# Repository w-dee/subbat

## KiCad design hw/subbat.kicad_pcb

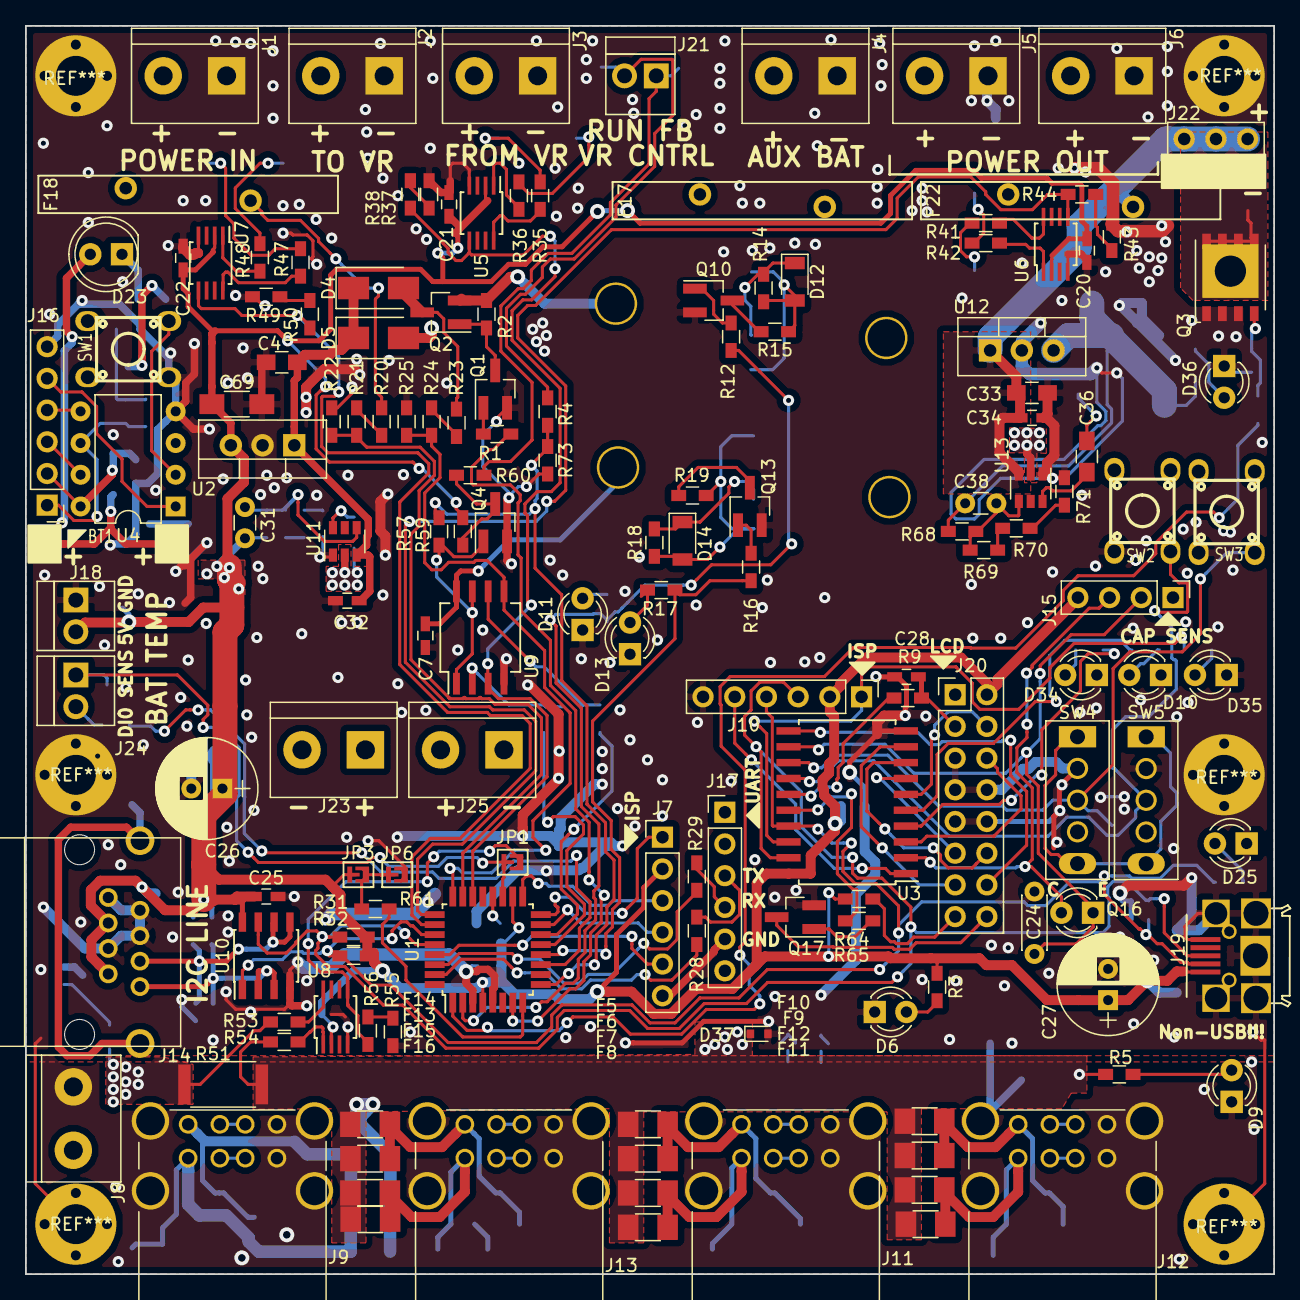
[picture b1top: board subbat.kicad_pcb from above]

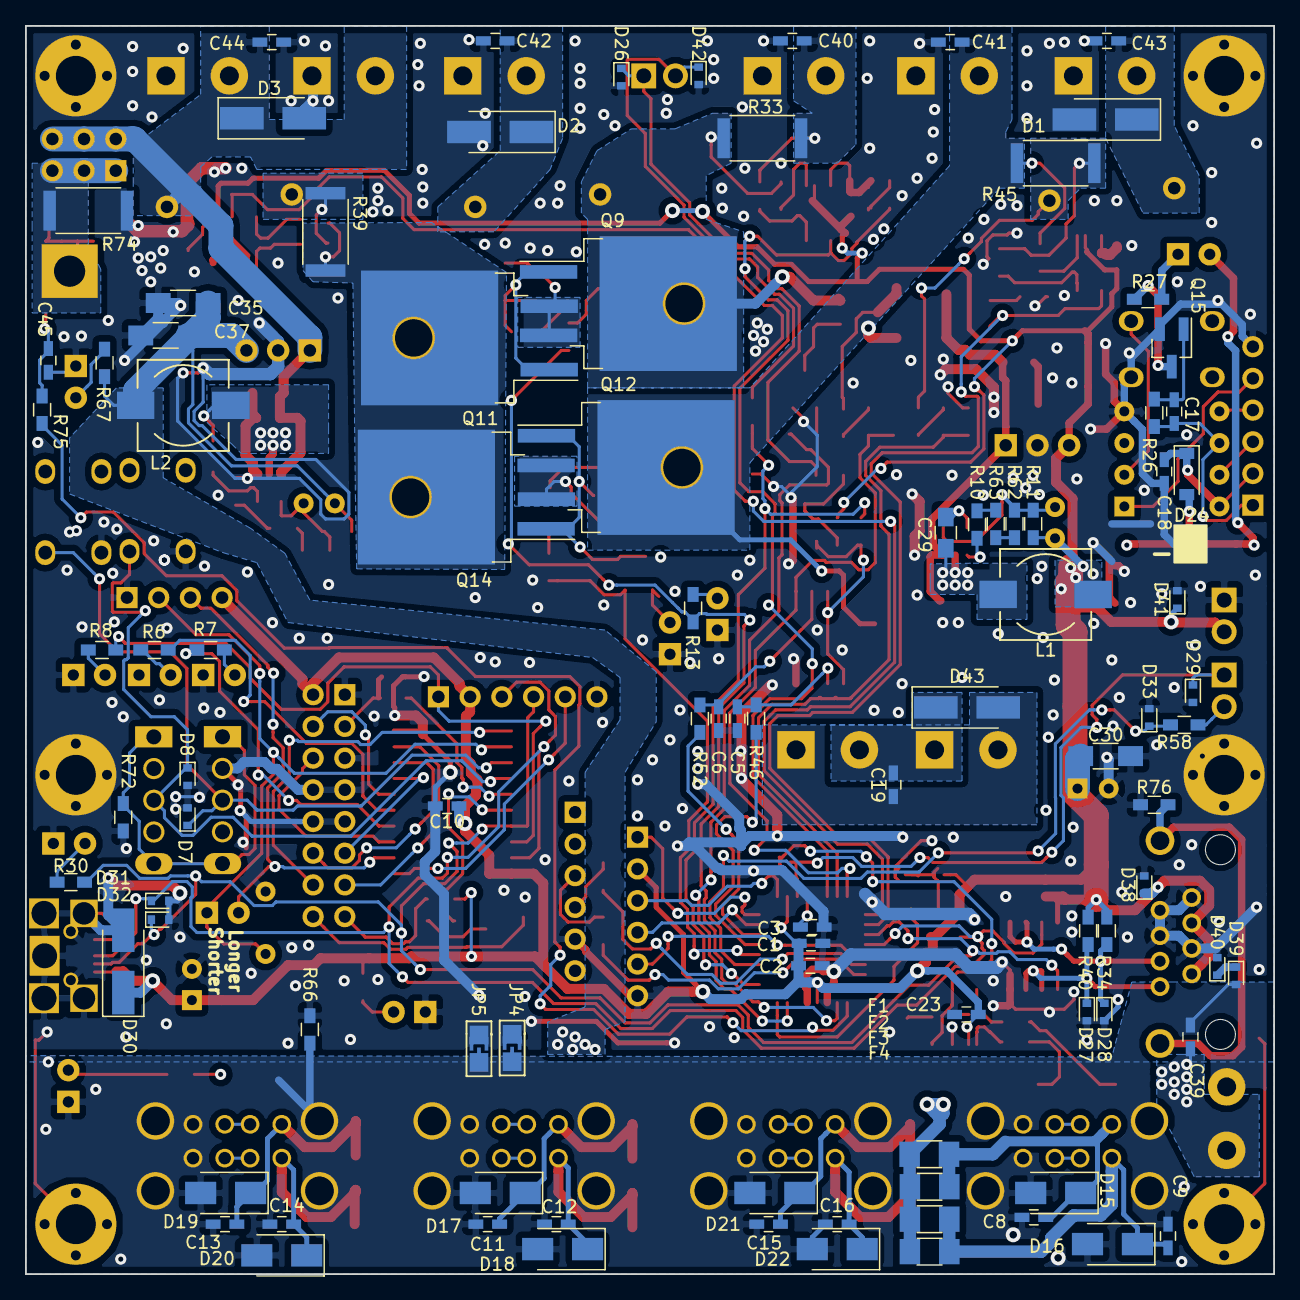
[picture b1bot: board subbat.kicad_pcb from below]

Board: 2 copper layers, 100.0 x 100.0 mm, 248 parts (95 on the bottom side), 149 nets.

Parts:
BT1: Battery_Cell; CR2032HOLDER_SIDE_SHORT
C1, C2, C3, C5, C6, C7, C8, C9, C10, C11, C12, C13, C14, C15, C16, C18, C19, C20, C21, C22, C23, C25, C28, C32, C34, C39, C40, C41, C42, C43, C44: 1u; C_0603_HandSoldering
C4, C33: 4.7u 50V; C_0805_HandSoldering
C17: 220p; C_0603_HandSoldering
C24: 0.1u; C_Disc_D4.3mm_W1.9mm_P5.00mm
C26: 100u; CP_Radial_D8.0mm_P2.50mm
C27: CP1_Small; CP_Radial_D8.0mm_P2.50mm
C29, C36: 0.1u 50V; C_0805_HandSoldering
C30, C35, C37, C69: 10u; C_1206_HandSoldering
C31, C38: 75p; C_Disc_D3.0mm_W1.6mm_P2.50mm
C45: 1u DNI; C_0603_HandSoldering
D1, D2, D3, D43: 30V; D_SMA_Handsoldering
D4, D5: D_Schottky; D_SMA
D6, D9, D10, D11, D13, D25, D34, D35, D36: LED; LED_D3.0mm
D7, D8, D26, D27, D28, D29, D31, D32, D33, D37, D38, D39, D40, D41, D42: ESD5Z5.0T1G; D_SOD-523
D12, D14: 12V; D_1206
D15, D16, D17, D18, D19, D20, D21, D22: 6V; D_SMA
D23: IR LED; LED_D5.0mm
D24: D_Schottky; D_SOD-123
D30: 6V; D_SMA_Handsoldering
F1, F2, F3, F4, F5, F6, F7, F8, F9, F10, F11, F12, F13, F14, F15, F16: 2A; Fuse_SMD1206_Wave
F17, F18, F22: 9A hold, 18A trip; POLYSWITCH_W24_P10
J1, J2, J3, J4, J5, J6, J8, J23, J25: Conn_01x02; TerminalBlock_bornier-2_P5.08mm
J7, J10, J16, J17: Conn_01x06_Male; Pin_Header_Straight_1x06_Pitch2.54mm
J9, J11, J12, J13: USB_Ax2
J14: RJ45; RJ45_8_Neltron-7810
J15: Conn_01x04_Male; Pin_Header_Straight_1x04_Pitch2.54mm
J18, J21, J24: Conn_01x02; TerminalBlock_2_P_2.54mm_without_hole
J19: USB_B_Micro; USB-MICRO-B-RECEPT-UNIVERSAL
J20: Conn_02x08_Odd_Even; Pin_Header_Straight_2x08_Pitch2.54mm
J22: Conn_02x03_Odd_Even; Pin_Header_Straight_2x03_Pitch2.54mm
JP1, JP3: Jumper_NO_Small; SolderJumper
JP4, JP5: Jumper_NO_Small; SolderJumper_L
JP6: Jumper_NC_Small; SolderJumper
L1, L2: 22u; Choke_SMD_7.3x7.3_H3.5_handsoldering
Q1, Q4, Q10, Q13, Q15, Q17: Q_NPN_BEC; SOT-23_Handsoldering
Q2: Q_PMOS_GSD; SOT-23_Handsoldering
Q3: TPH11006NL; TDSON-8-1_HandSoldering_mod
Q9, Q11, Q12, Q14: AOD403; TO-263-2-with-holes
Q16: Q_Photo_NPN_EC; LED_D3.0mm
R1, R12, R15, R16, R19, R21, R24, R26, R57, R59, R62, R65, R69, R73: 10k; R_0603_HandSoldering
R2, R14, R18, R66: 470k; R_0603_HandSoldering
R3, R4, R5, R6, R7, R8, R13, R17, R30, R60, R63, R67, R70: 2.2k; R_0603_HandSoldering
R9, R11, R46, R52, R68: 100k; R_0603_HandSoldering
R10, R22, R25, R34, R37, R40, R43, R49, R55, R71: 1k; R_0603_HandSoldering
R20, R23, R61: 22k; R_0603_HandSoldering
R27, R75: 10R; R_0603_HandSoldering
R28, R29, R35, R36, R38, R41, R42, R44, R47, R48, R50, R53, R54, R56, R58: 120R; R_0603_HandSoldering
R31, R32: 4.7k; R_0603_HandSoldering
R33, R39, R45, R51: 0.01R; R_2512
R64: 680; R_0603_HandSoldering
R72, R76: 1M; R_0603_HandSoldering
R74: 10R 2W@long, 20W@1 sec; R_2512
SW1, SW2, SW3: SW_Push; TACT-SW-4P
SW4, SW5: SW_SPDT_WITH_SHIELD; SW_SPDT_WITH_SHILD
U1: ATMEGA328P-AU; TQFP-32_7x7mm_Pitch0.8mm
U2, U12: L7803; TO-220-3_Vertical
U3: ATTINY2313-20SU; SOIC-20W_7.5x12.8mm_Pitch1.27mm
U4: ATTINY13A-SSU; DIP-8_W7.62mm
U5, U6, U7, U8: LT6105; MSOP-8_3x3mm_Pitch0.65mm-thin
U9: LM393; SO-8_5.3x6.2mm_Pitch1.27mm
U10: P82B96; SOIC-8_3.9x4.9mm_Pitch1.27mm
U11, U13: TPS54202; SOT-23-6

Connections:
+5V: C1.1, C2.1, C10.1, C20.1, C21.1, C22.1, C23.1, C25.1, C26.1, C27.1, C30.1, C31.1, C69.1, D30.1, D38.1, D41.1, J7.2, J10.2, J14.2, J14.6, J15.4, J18.2, J19.1, J20.2, JP3.2, L1.1, R3.1, R11.1, R31.1, R32.1, R34.1, R40.1, R59.2, R64.1, U1.4, U1.18, U2.3, U3.20, U5.2, U6.2, U7.2, U8.2, U10.8
/BAT_TEMP_SENS: D29.1, J24.1, JP1.2, U1.19
/BiDiSwitch3/COM_SRC: D12.1, Q9.3, Q11.3, R14.1
/BiDiSwitch4/COM_SRC: D14.1, Q12.3, Q14.3, R18.1
/CCCV_FEEDBACK: D26.1, J21.1, R60.2
/CCCV_IN: C40.2, J3.2, R33.2, R35.1
/CC_CTRL: R46.1, U1.13
/CV_CTRL: R52.1, U1.14
/DIGITAL_IN0: D33.1, R58.1, U1.11
/ICHARGE_SENS: R38.2, U1.22, U5.5, U9.3
/IOUT_SENS: R44.2, U1.25, U6.5
/ISYS_SENS: R50.2, U1.26, U7.5
/IUSB_SENS: JP1.1, R56.2, U8.5
/MISO: J7.1, U1.16
/MOSI: J7.4, U1.15
/MS: JP3.1, JP6.2, R61.2
/OUTCAP_CHARGE: R75.2, U1.1
/OUTCAP_N: J22.1, J22.3, J22.5, Q3.5, Q3.6, Q3.7, Q3.8, R74.1
/PT_N: C19.1, D43.2, J23.2, J25.1
/PT_P: C19.2, D43.1, J23.1, J25.2
/Power5V/REG_IN: C4.1, C32.1, D4.1, D5.1, U2.1, U11.3
/Power5V/VSW: C29.2, L1.2, U11.2
/Power5V/VSW2: C36.2, L2.2, U13.2
/RX: R29.1, U1.30
/SCK: J7.3, U1.17
/SCL_L: D28.1, J14.3, R34.2, U10.5, U10.6
/SDA_L: D27.1, J14.1, R40.2, U10.2, U10.3
/SW_BAT: R12.2, R13.1, U1.2
/SW_VR: R4.2, R57.2, R73.1, U1.9
/SW_VS: R16.2, R17.1, U1.12
/SingleButtonRemocon/LED_OUT: C17.2, J16.1, R26.2, U4.6
/SingleButtonRemocon/MOSI: J16.4, U4.5
/SingleButtonRemocon/SCK: J16.3, U4.7
/SingleButtonRemocon/VBAT3V3: BT1.1, D23.2, D24.2
/SingleButtonRemocon/VMCU3V3: C18.1, D24.1, J16.2, U4.8
/SingleButtonRemocon/~RESET: J16.5, U4.1
/TX: R28.1, U1.31
/VA: F17.1, Q2.2, Q9.2, R2.1, R33.1, R36.1
/VA2: C42.2, D2.1, F17.2, J4.2
/VA_G: D4.2, Q2.3, R23.1
/VA_SENSE_ADC: R24.2, R25.1, U1.24, U9.5
/VBUS_COM_IN: C39.2, J8.2, R51.2, R53.1
/VOUT: Q11.2, Q14.2, R39.2, R41.1
/VOUT2: C33.1, C34.1, C44.2, D3.1, F22.2, J5.2, J6.2, J22.2, J22.4, J22.6, U12.1, U13.3
/VOUTM: F22.1, R39.1, R42.1
/VS: F18.2, R20.1, R45.2, R47.1
/VS2: C7.1, C41.2, D5.2, J2.2, Q12.2, R45.1, R48.1, U9.8
/VSIN: C43.1, D1.1, F18.1, J1.2
/VS_SENSE_ADC: R21.2, R22.1, U1.23
/WaterLevel/ALLOW_DISCHG: D7.1, SW3.2, SW4.2, U3.13
/WaterLevel/CHARGE: J15.3, Q16.2, U3.2
/WaterLevel/LCD_CONTRAST: R9.1, U3.15
/WaterLevel/LCD_D4: J20.11, U3.7
/WaterLevel/LCD_D5: J20.12, U3.8
/WaterLevel/LCD_D6: J20.13, U3.9
/WaterLevel/LCD_D7: J20.14, U3.11
/WaterLevel/LCD_E: J20.6, U3.3
/WaterLevel/LCD_RS: J20.4, U3.6
/WaterLevel/LED_LCD_PWM: R65.1, U3.16
/WaterLevel/MISO: J10.1, R8.1, U3.18
/WaterLevel/PREFER_DISCHG: D8.1, SW2.2, SW5.2, U3.14
/WaterLevel/SENS: C24.1, J15.2, Q16.1, U3.12
/WaterLevel/~RESET: J10.5, U3.1
/~DEEP_SLEEP_EN: R1.2, U1.7
/~RESET: J7.5, U1.29
BUSGND: C8.2, C9.2, C11.2, C12.2, C13.2, C14.2, C15.2, C16.2, C39.1, D9.1, D15.2, D16.2, D17.2, D18.2, D19.2, D20.2, D21.2, D22.2, D39.2, J8.1, J9.4, J9.8, J9.9, J11.4, J11.8, J11.9, J12.4, J12.8, J12.9, J13.4, J13.8, J13.9, JP4.2, JP5.2, R66.1
GND: BT1.2, C1.2, C2.2, C3.2, C4.2, C5.2, C6.2, C7.2, C10.2, C18.2, C20.2, C21.2, C22.2, C23.2, C24.2, C25.2, C26.2, C27.2, C28.2, C30.2, C32.2, C33.2, C34.2, C35.2, C37.2, C40.1, C41.1, C42.1, C43.2, C44.1, C45.1, C69.2, D1.2, D2.2, D3.2, D6.1, D7.2, D8.2, D10.1, D11.1, D13.1, D25.1, D26.2, D27.2, D28.2, D29.2, D30.2, D31.2, D32.2, D33.2, D34.1, D35.1, D36.1, D37.2, D38.2, D40.2, D41.2, D42.2, J1.1, J2.1, J3.1, J4.1, J5.1, J6.1, J7.6, J10.6, J14.4, J14.5, J14.7, J14.8, J15.1, J16.6, J17.5, J18.1, J19.5, J19.6, J20.1, J20.5, J20.7, J20.8, J20.9, J20.10, JP4.1, JP5.1, JP6.1, Q1.2, Q3.1, Q3.2, Q3.3, Q4.2, Q10.2, Q13.2, Q15.2, Q17.2, R10.2, R22.2, R25.2, R37.2, R43.2, R49.2, R55.2, R66.2, R71.2, R72.2, R73.2, R74.2, R76.2, SW1.1, SW2.1, SW3.1, SW4.1, SW5.1, U1.3, U1.5, U2.2, U3.10, U4.4, U5.4, U6.4, U7.4, U8.4, U9.4, U10.4, U11.1, U12.2, U13.1
unnamed: C3.1, U1.20
unnamed: C5.1, R46.2, U9.2
unnamed: C6.1, R52.2, U9.6
unnamed: C8.1, D15.1, F1.1, F2.1, J9.1
unnamed: C9.1, D16.1, F3.1, F4.1, J9.5
unnamed: C11.1, D17.1, F5.1, F6.1, J11.1
unnamed: C12.1, D18.1, F7.1, F8.1, J11.5
unnamed: C13.1, D19.1, F9.1, F10.1, J12.1
unnamed: C14.1, D20.1, F11.1, F12.1, J12.5
unnamed: C15.1, D21.1, F13.1, F14.1, J13.1
unnamed: C16.1, D22.1, F15.1, F16.1, J13.5
unnamed: C17.1, Q15.1, R26.1
unnamed: C28.1, J20.3, R9.2
unnamed: C29.1, U11.6
unnamed: C31.2, R11.2, R62.1, U11.4
unnamed: C36.1, U13.6
unnamed: C38.2, R68.2, R69.1, U13.4
unnamed: C45.2, Q3.4, R75.1
unnamed: D6.2, R3.2
unnamed: D9.2, R5.2
unnamed: D10.2, R6.2
unnamed: D11.2, R13.2
unnamed: D12.2, Q9.1, Q11.1, R14.2, R15.1
unnamed: D13.2, R17.2
unnamed: D14.2, Q12.1, Q14.1, R18.2, R19.1
unnamed: D23.1, R27.1
unnamed: D25.2, R30.2
unnamed: D34.2, R7.2
unnamed: D35.2, R8.2
unnamed: D36.2, R67.2
unnamed: D39.1, D40.1
unnamed: D42.1, J21.2, R4.1
unnamed: J9.2, J9.3
unnamed: J9.6, J9.7
unnamed: J11.2, J11.3
unnamed: J11.6, J11.7
unnamed: J12.2, J12.3
unnamed: J12.6, J12.7
unnamed: J13.2, J13.3
unnamed: J13.6, J13.7
unnamed: J14.9, R76.1
unnamed: J17.3, R28.2
unnamed: J17.4, R29.2
unnamed: J20.15, R64.2
unnamed: J20.16, Q17.3
unnamed: J24.2, R58.2
unnamed: Q1.1, R1.1
unnamed: Q1.3, Q2.1, R2.2
unnamed: Q4.1, R57.1, U9.1, U9.7
unnamed: Q4.3, R59.1, R60.1
unnamed: Q10.1, R12.1
unnamed: Q10.3, R15.2
unnamed: Q13.1, R16.1
unnamed: Q13.3, R19.2
unnamed: Q15.3, R27.2
unnamed: Q17.1, R65.2
unnamed: R6.1, U3.5
unnamed: R7.1, U3.4
unnamed: R10.1, R63.2
unnamed: R20.2, R21.1
unnamed: R23.2, R24.1
unnamed: R35.2, U5.8
unnamed: R36.2, U5.1
unnamed: R37.1, R38.1
unnamed: R41.2, U6.8
unnamed: R42.2, U6.1
unnamed: R43.1, R44.1
unnamed: R47.2, U7.8
unnamed: R48.2, U7.1
unnamed: R49.1, R50.1
unnamed: R53.2, U8.8
unnamed: R54.2, U8.1
unnamed: R55.1, R56.1
unnamed: R61.1, U1.8
unnamed: R62.2, R63.1
unnamed: R69.2, R70.1
unnamed: R70.2, R71.1
unnamed: R72.1, SW4.4, SW4.5, SW5.4, SW5.5
unnamed: SW1.2, U4.2
SCL: D31.1, J10.3, J19.3, R31.2, U1.28, U3.19, U10.7
SDA: D32.1, J10.4, J19.2, R30.1, R32.2, U1.27, U3.17, U10.1
VCOM: C35.1, C37.1, C38.1, D37.1, F1.2, F2.2, F3.2, F4.2, F5.2, F6.2, F7.2, F8.2, F9.2, F10.2, F11.2, F12.2, F13.2, F14.2, F15.2, F16.2, L2.1, R5.1, R51.1, R54.1, R67.1, R68.1, U12.3

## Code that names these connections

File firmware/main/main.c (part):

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SYS->OUT 10.0A | AMB 20.1C 54% 1023h
C-CHARGE 12.0V 10.3A | BAT 11.0V 19C

C: constant current charge
V: constant voltage charge
F: floating charge
*/

#define CURRENT_SENS_REGISTER 0.01 // current sens register value
#define CURRENT_SENS_GAIN ((4700.0 + 680.0) / 120.0)

static float current_to_reading_voltage(float current)
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#define BATTERY_MIN_VOLTAGE 0.0 //9.0 // battery voltage (no matter the battery is loaded/charging/open) below this voltage
								// immediately shuts down the system

#define BATTERY_CHARGE_END_CURRENT 0.03 // battery charge finish current

/* ポートマップの定義 */
MAP_START(pmap)
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pmap('D', 2, MDI);  // 4 PD2 (PCINT18/INT0)       SCL
#define OUTPUT_CHARGE 'D', 3
pmap('D', 3, MDO0); // 5 PD3 (PCINT19/OC2B/INT1)  OUTPUT_CHARGE
#define SW_BAT 'D', 4
pmap('D', 4, MDO0); // 6 PD4 (PCINT20/XCK/T0)     SW_BAT
                    // 7 VCC
                    // 8 GND
#define DEEP_SLEEP_EN 'B', 6
pmap('B', 6, MDO1); // 9 PB6 (PCINT6/XTAL1/TOSC1) /DEEP_SLEEP_EN
#define SW_CHG 'B', 7
pmap('B', 7, MDI);  //10 PB7 (PCINT7/XTAL2/TOSC2) SW_CHG
#define SW_VR 'D', 5
pmap('D', 5, MDO0); //11 PD5 (PCINT21/OC0B/T1)    SW_VR
pmap('D', 6, MDI);  //12 PD6 (PCINT22/OC0A/AIN0)  SDA
pmap('D', 7, MDI);  //13 PD7 (PCINT23/AIN1)       DIGITAL_IN0
#define SW_VS  'B', 0
pmap('B', 0, MDO0); //14 PB0 (PCINT0/CLKO/ICP1)   SW_VS
pmap('B', 1, MDO0); //15 PB1 (OC1A/PCINT1)        CC_CTRL
pmap('B', 2, MDO0); //16 PB2 (SS/OC1B/PCINT2)     CV_CTRL
pmap('B', 3, MDO0); //17 PB3 (MOSI/OC2A/PCINT3)   MOSI
pmap('B', 4, MDO0); //18 PB4 (MISO/PCINT4)        MISO
pmap('B', 5, MDO0); //19 PB5 (SCK/PCINT5)         SCK
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#define ADC_CH_ISYS_SENSE 3
pmap('C', 3, MAI);  //26 PC3 (ADC3/PCINT11)       ISYS sense
#define ADC_CH_VR_SENSE 4
pmap('C', 4, MAI);  //27 PC4 (ADC4/SDA/PCINT12)   VR output voltage sens
#define ADC_CH_VDD_SENSE 5
pmap('C', 5, MAI);  //28 PC5 (ADC5/SCL/PCINT13)   
#define ADC_CH_IUSB_SENSE 6
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		.dark_ambient = 120,
		.pwm_light = 50,
		.pwm_dark = 12,
		.lcd_contrast = 20,
	};

static void eeprom_copy()
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			if(battery_raw_voltage < eeprom.chg_restart)
			{
				// the battery raw voltage is below restarting voltage;
				// do constant-current, constant voltage charge
				battery_charge_fsm_state = bcfsChargeCCCV;
				debug_send_P(PSTR("\r\nbcfsChargeCCCV\r\n"));
				set_battery_cc_cv_param();
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
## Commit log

2018-01-25 Added current sensors; and other many modifications
2018-01-28 Some architectual changes
2018-01-28 Use voltage regulator's RUN(EN) control for enable/disable CCCV output
2018-01-29 Layout in advance
2018-01-30 Component rearrangement from scratch; DRC clear
2018-02-01 Added resettable fuses; DRC clear
2018-02-05 To use RJ45 connector to join Main/Sub MCUs; DRC clear
2018-02-07 Added output cap soft start circuit; DRC clear
2018-02-08 some improvements; DRC clear
2018-02-10 Final Revision; PCB ordered using this version
2018-02-14 Added lcd/ and sub/ sub-processor directories; fiexed Makefile
2018-02-14 Updated .gitignore
2018-02-23 Various changes; Sorry that the commit granule gets too large
2018-02-24 Applied current to date schematic (PCB layout is to be not to date for a while)
2018-03-29 Added annotation to date
2018-03-29 Testing using prototype board
2018-04-09 Added dot definition constants; experimental
2018-04-09 Minor fixes
2018-04-09 CCCV mode almost complete
2018-04-13 To be able to reset
2018-04-13 NCT75 suppport added; CCCV mode almost completed
